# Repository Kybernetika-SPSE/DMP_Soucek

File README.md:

## Cíl práce
Cílem maturitní práce je navrhnout a vytvořit zařízení pro přesné měření času na závodní dráze. Součástí systému bude displej, který umožní nejen ovládání celé dráhy, ale také bude zobrazovat aktuální čas měřený během závodu. Zařízení by mělo zajistit jednoduché uživatelské rozhraní a spolehlivou funkčnost, aby bylo vhodné pro závodní podmínky.

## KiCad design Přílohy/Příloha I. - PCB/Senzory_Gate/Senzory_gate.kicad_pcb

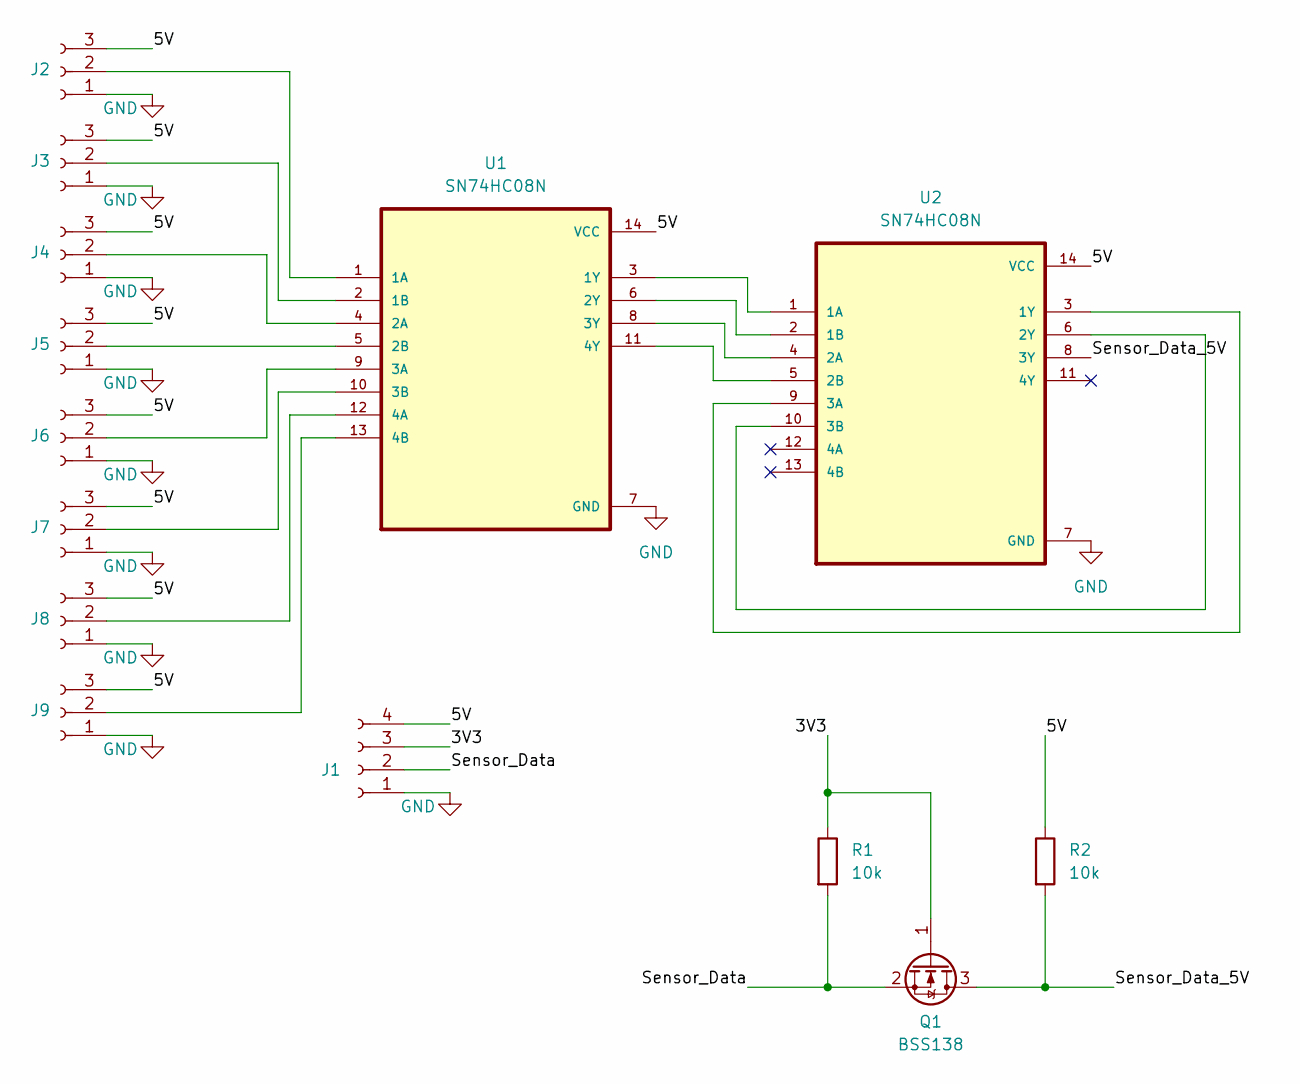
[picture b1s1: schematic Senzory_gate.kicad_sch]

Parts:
J1: Conn_01x04_Socket; JST_EH_B4B-EH-A_1x04_P2.50mm_Vertical
J2, J3, J4, J5, J6, J7, J8, J9: Conn_01x03_Socket; JST_EH_B3B-EH-A_1x03_P2.50mm_Vertical
Q1: BSS138; SOT-23
R1, R2: 10k; R_0603_1608Metric_Pad0.98x0.95mm_HandSolder
U1, U2: SN74HC08N; DIP794W45P254L1969H508Q14

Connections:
/3V3: J1.3, Q1.1 (G), R1.1
/5V: J1.4, J2.3, J3.3, J4.3, J5.3, J6.3, J7.3, J8.3, J9.3, R2.1, U1.14 (VCC), U2.14 (VCC)
/Sensor_Data: J1.2, Q1.2 (S), R1.2
/Sensor_Data_5V: Q1.3 (D), R2.2, U2.8 (3Y)
GND: J1.1, J2.1, J3.1, J4.1, J5.1, J6.1, J7.1, J8.1, J9.1, U1.7 (GND), U2.7 (GND)
unnamed: J2.2, U1.1 (1A)
unnamed: J3.2, U1.2 (1B)
unnamed: J4.2, U1.4 (2A)
unnamed: J5.2, U1.5 (2B)
unnamed: J6.2, U1.9 (3A)
unnamed: J7.2, U1.10 (3B)
unnamed: J8.2, U1.12 (4A)
unnamed: J9.2, U1.13 (4B)
unnamed: U1.3 (1Y), U2.1 (1A)
unnamed: U1.6 (2Y), U2.2 (1B)
unnamed: U1.8 (3Y), U2.4 (2A)
unnamed: U1.11 (4Y), U2.5 (2B)
unnamed: U2.3 (1Y), U2.9 (3A)
unnamed: U2.6 (2Y), U2.10 (3B)

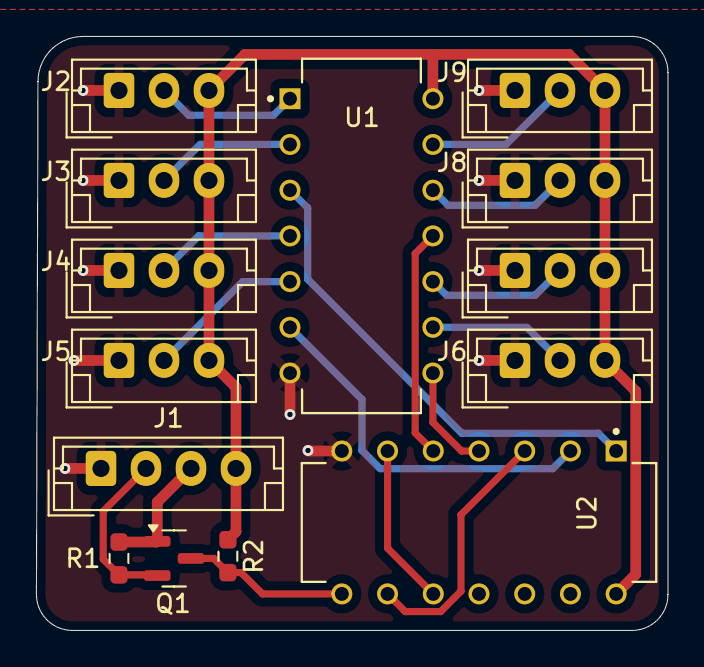
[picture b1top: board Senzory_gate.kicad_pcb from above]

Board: 2 copper layers, 35.1 x 33.0 mm, 14 parts (0 on the bottom side), 19 nets.

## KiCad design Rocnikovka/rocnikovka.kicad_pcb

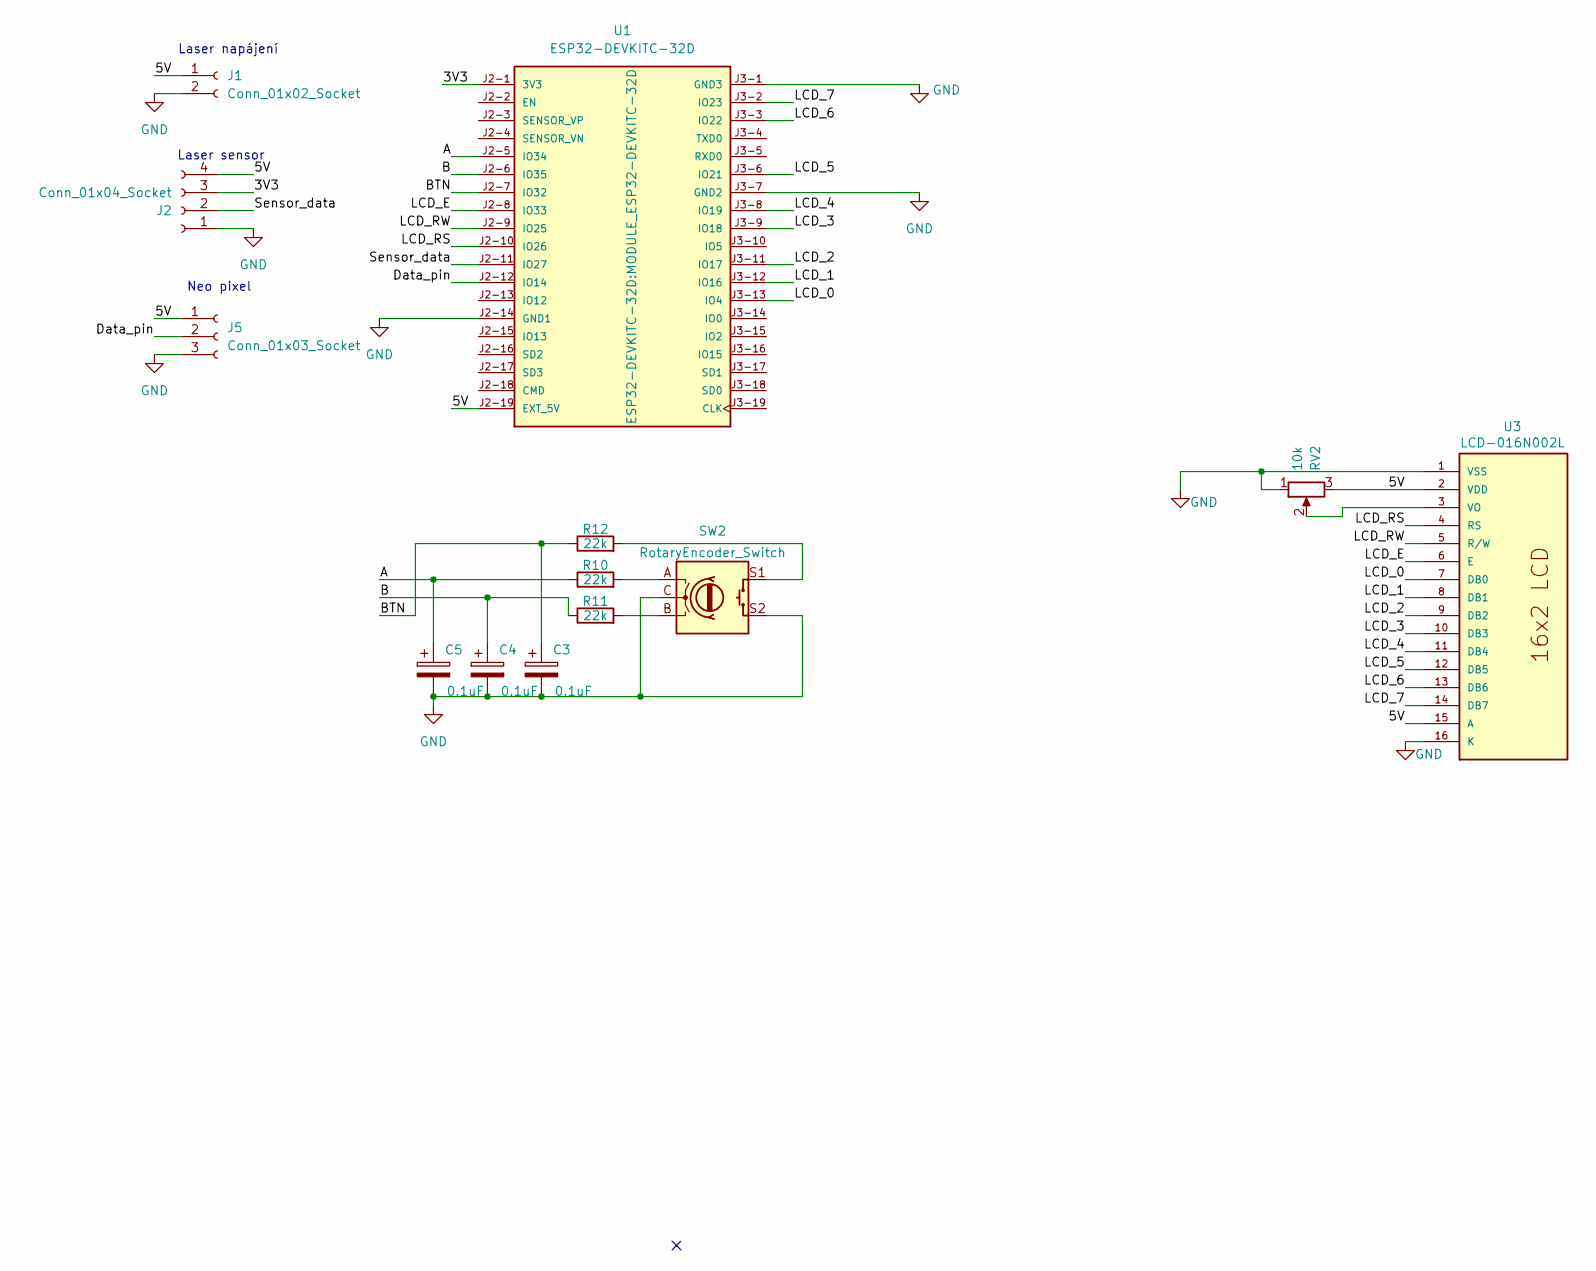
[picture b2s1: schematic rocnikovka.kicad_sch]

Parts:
C3, C4, C5: 0.1uF; C_0805_2012Metric_Pad1.18x1.45mm_HandSolder
J1: Conn_01x02_Socket; JST_EH_B2B-EH-A_1x02_P2.50mm_Vertical
J2: Conn_01x04_Socket; JST_EH_B4B-EH-A_1x04_P2.50mm_Vertical
J5: Conn_01x03_Socket; JST_EH_B3B-EH-A_1x03_P2.50mm_Vertical
R10, R11, R12: 22k; R_0805_2012Metric_Pad1.20x1.40mm_HandSolder
RV2: 10k; Potentiometer_ACP_CA6-VSMD_Vertical
SW2: RotaryEncoder_Switch; RotaryEncoder_Alps_EC11E-Switch_Vertical_H20mm_CircularMoun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
U1: ESP32-DEVKITC-32D; MODULE_ESP32-DEVKITC-32D; PARTREV V4
U3: LCD-016N002L; MODULE_LCD-16X2; PARTREV N/A

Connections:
/3V3: J2.3, U1.J2-1 (3V3)
/5V: J1.1, J2.4, J5.1, RV2.3, U1.J2-19 (EXT_5V), U3.2 (VDD), U3.15 (A)
/A: C5.1, R10.1, U1.J2-5 (IO34)
/B: C4.1, R11.1, U1.J2-6 (IO35)
/BTN: C3.1, R12.1, U1.J2-7 (IO32)
/Data_pin: J5.2, U1.J2-12 (IO14)
/LCD_0: U1.J3-13 (IO4), U3.7 (DB0)
/LCD_1: U1.J3-12 (IO16), U3.8 (DB1)
/LCD_2: U1.J3-11 (IO17), U3.9 (DB2)
/LCD_3: U1.J3-9 (IO18), U3.10 (DB3)
/LCD_4: U1.J3-8 (IO19), U3.11 (DB4)
/LCD_5: U1.J3-6 (IO21), U3.12 (DB5)
/LCD_6: U1.J3-3 (IO22), U3.13 (DB6)
/LCD_7: U1.J3-2 (IO23), U3.14 (DB7)
/LCD_E: U1.J2-8 (IO33), U3.6 (E)
/LCD_RS: U1.J2-10 (IO26), U3.4 (RS)
/LCD_RW: U1.J2-9 (IO25), U3.5 (R/W)
/Sensor_data: J2.2, U1.J2-11 (IO27)
GND: C3.2, C4.2, C5.2, J1.2, J2.1, J5.3, RV2.1, SW2.C, SW2.S2, U1.J2-14 (GND1), U1.J3-1 (GND3), U1.J3-7 (GND2), U3.1 (VSS), U3.16 (K)
unnamed: R10.2, SW2.A
unnamed: R11.2, SW2.B
unnamed: R12.2, SW2.S1
unnamed: RV2.2, U3.3 (VO)

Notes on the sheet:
Laser sensor
Neo pixel
Laser napájení

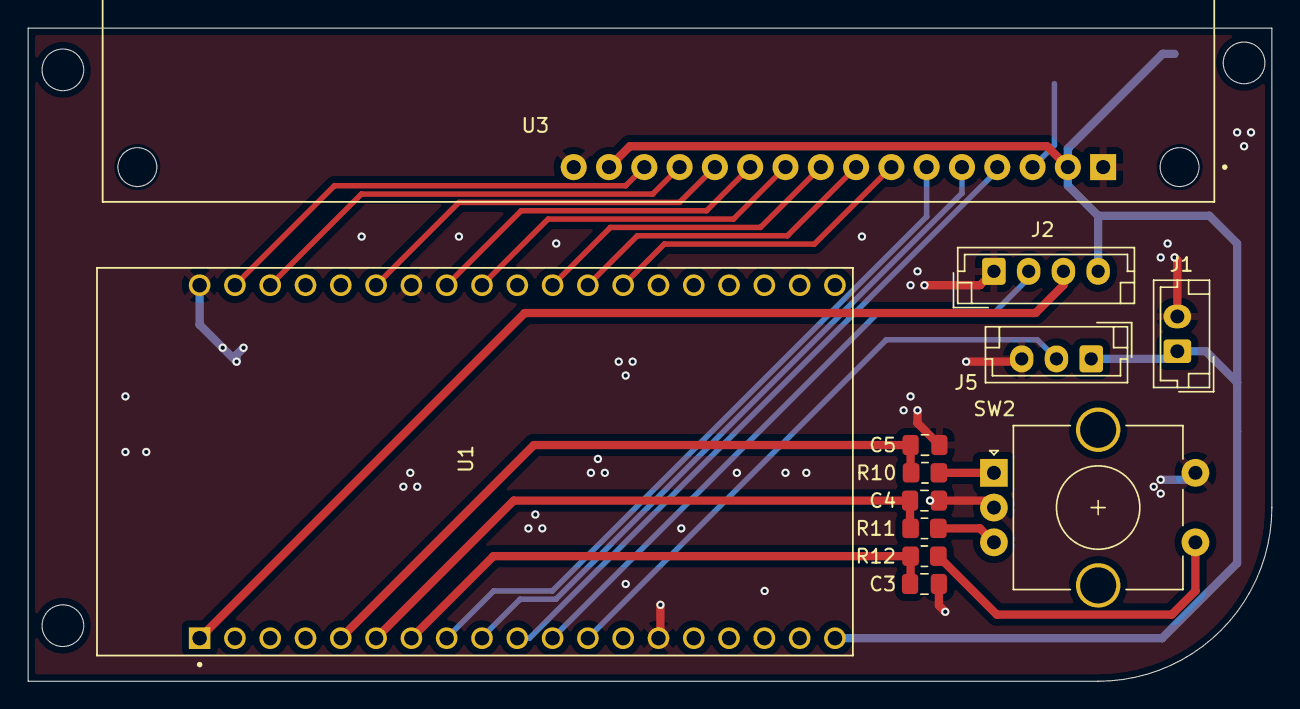
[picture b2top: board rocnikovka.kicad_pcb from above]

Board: 2 copper layers, 89.5 x 47.0 mm, 13 parts (1 on the bottom side), 23 nets.

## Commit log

2024-10-30 Create Update_zari_rijen
2024-10-30 Create UPDATE
2024-10-30 Rename Pokrok v maturitní práci 1.pdf to Pokrok_DMP_rijen.pdf
2025-01-13 Rename Pokrok v maturitní práci 2.pdf to Pokrok v maturitní práci - prosinec.pdf
2025-01-13 Rename Pokrok v maturitní práci - prosinec.pdf to Pokrok_DMP_prosinec.pdf
2025-01-14 Create PCB
2025-01-20 Přidání PCB
2025-02-10 PCB_2
2025-04-06 Create Přílohy
2025-04-10 Náhraní všecho
    blablabla
